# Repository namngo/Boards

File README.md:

# boards

## V1 

### Scope:

#### PCB

1. Use Esp32-s3 devboard.
1. Power directly from battery, not through battery pack (buck converter).
1. Front light: led driver.
1. Sensor: temperature.
1. LCD for information.
1. Box.
1. Button for light: off, auto, on.
1. Water proof.

Nice: Charge from bike charger.

Nice to have:

1. Backlight (red).
1. Button controller.

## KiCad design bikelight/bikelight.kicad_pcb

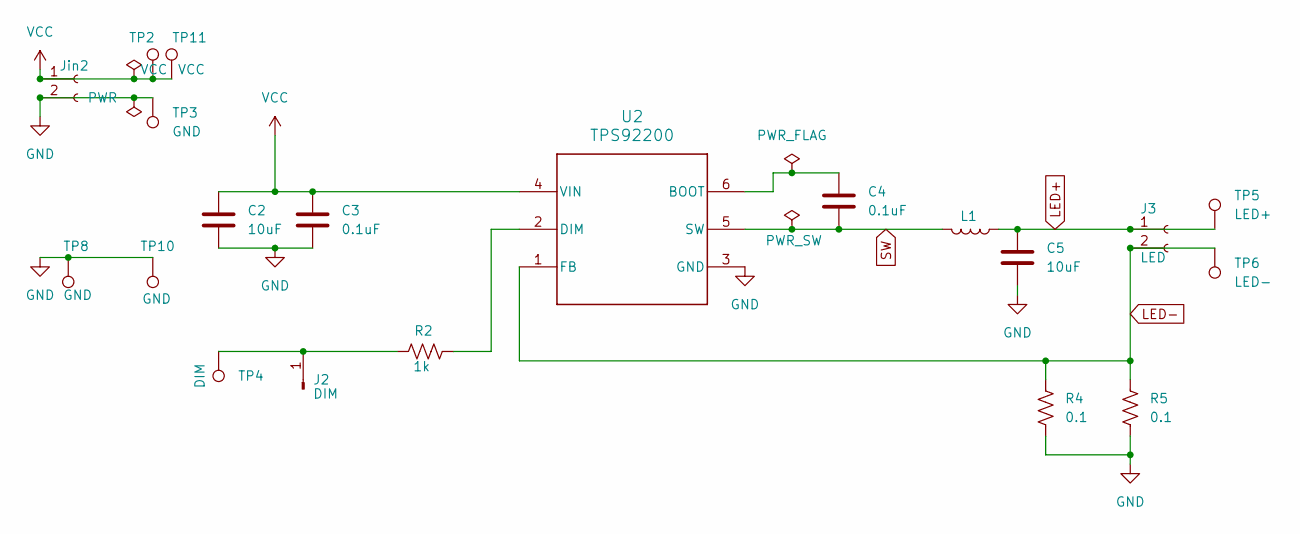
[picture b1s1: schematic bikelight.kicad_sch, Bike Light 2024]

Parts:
C2, C5: 10uF; C_1210_3225Metric
C3, C4: 0.1uF; C_0805_2012Metric
J2: DIM; PinHeader_1x01_P2.54mm_Vertical
J3: LED; PinHeader_1x02_P2.54mm_Vertical
Jin2: PWR; PinHeader_1x02_P2.54mm_Vertical
L1: L_Bourns_SRR1260
R2: 1k; R_0805_2012Metric
R4, R5: 0.1; R_1206_3216Metric
TP2, TP11: VCC; TestPoint_Pad_1.5x1.5mm
TP3, TP8, TP10: GND; TestPoint_Pad_1.5x1.5mm
TP4: DIM; TestPoint_Pad_1.5x1.5mm
TP5: LED+; TestPoint_Pad_1.5x1.5mm
TP6: LED-; TestPoint_Pad_1.5x1.5mm
U2: TPS92200; DDC0006A_N

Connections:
GND: C2.2, C3.2, C5.2, Jin2.2, R4.1, R5.1, TP3.1, TP8.1, TP10.1, U2.3 (GND)
LED+: C5.1, J3.1, L1.1, TP5.1
LED-: J3.2, R4.2, R5.2, TP6.1, U2.1 (FB)
unnamed: J2.1, R2.2, TP4.1
unnamed: C4.1, U2.6 (BOOT)
unnamed: R2.1, U2.2 (DIM)
SW: C4.2, L1.2, U2.5 (SW)
VCC: C2.1, C3.1, Jin2.1, TP2.1, TP11.1, U2.4 (VIN)

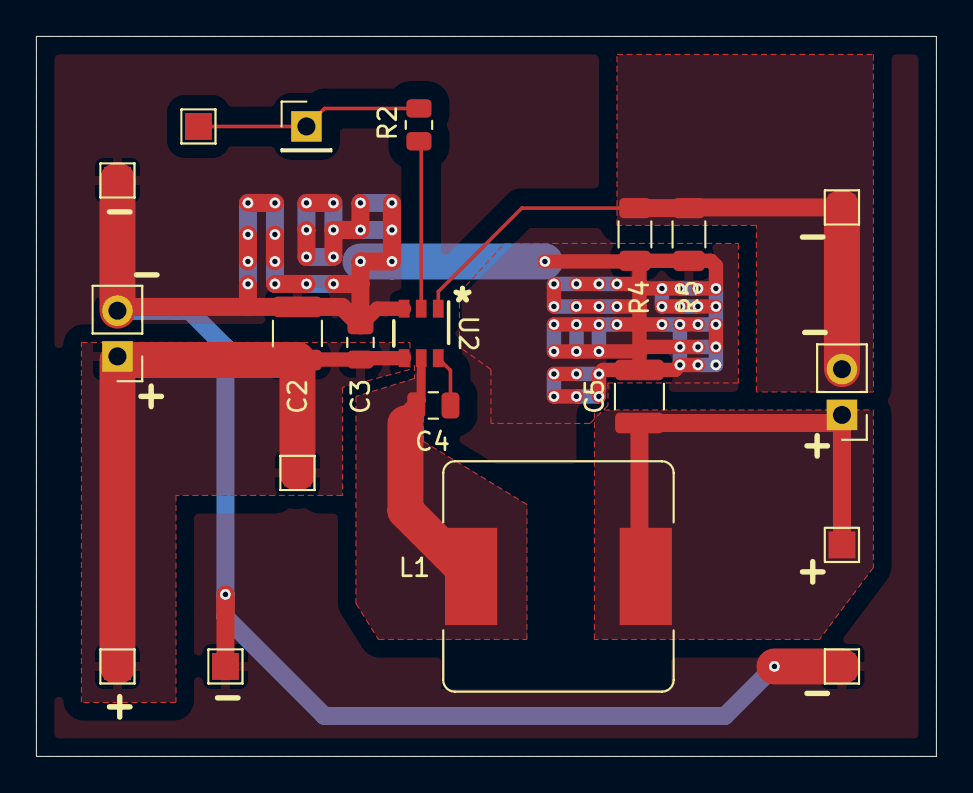
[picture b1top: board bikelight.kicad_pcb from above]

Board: 2 copper layers, 50.0 x 40.0 mm, 20 parts (0 on the bottom side), 8 nets.

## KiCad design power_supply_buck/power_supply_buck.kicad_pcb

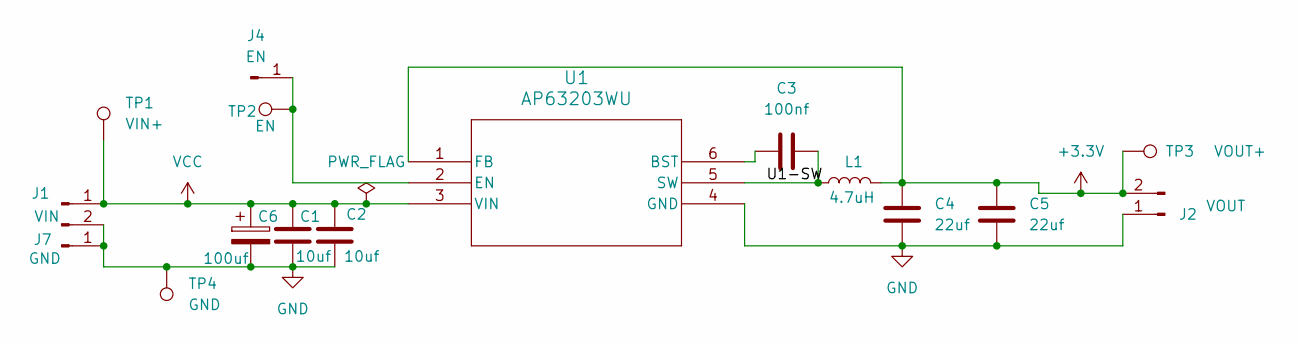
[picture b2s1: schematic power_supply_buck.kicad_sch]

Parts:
C1, C2: 10uf; C_1210_3225Metric_Pad1.33x2.70mm_HandSolder
C3: 100nf; C_0805_2012Metric_Pad1.18x1.45mm_HandSolder
C4, C5: 22uf; C_1210_3225Metric_Pad1.33x2.70mm_HandSolder
C6: 100uf; C_Elec_6.3x7.7
J1: VIN; PinHeader_1x02_P2.54mm_Vertical
J2: VOUT; PinHeader_1x02_P2.54mm_Vertical
J4: EN; PinHeader_1x01_P1.00mm_Vertical
J7: GND; PinHeader_1x01_P1.00mm_Vertical
L1: 4.7uH; L_Bourns_SRR1260
TP1: VIN+; TestPoint_Pad_1.0x1.0mm
TP2: EN; TestPoint_Pad_1.0x1.0mm
TP3: VOUT+; TestPoint_Pad_1.0x1.0mm
TP4: GND; TestPoint_Pad_1.0x1.0mm
U1: AP63203WU; AP63203WU-7_DIO

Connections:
+3.3V: C4.1, C5.1, J2.2, L1.2, TP3.1, U1.1 (FB)
/U1-SW: C3.2, L1.1, U1.5 (SW)
GND: C1.2, C2.2, C4.2, C5.2, C6.2, J1.2, J2.1, J7.1, TP4.1, U1.4 (GND)
unnamed: J4.1, TP2.1, U1.2 (EN)
unnamed: C3.1, U1.6 (BST)
VCC: C1.1, C2.1, C6.1, J1.1, TP1.1, U1.3 (VIN)

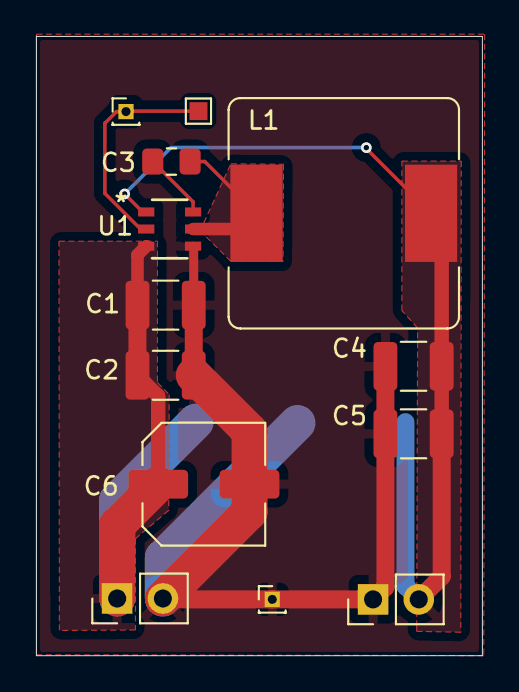
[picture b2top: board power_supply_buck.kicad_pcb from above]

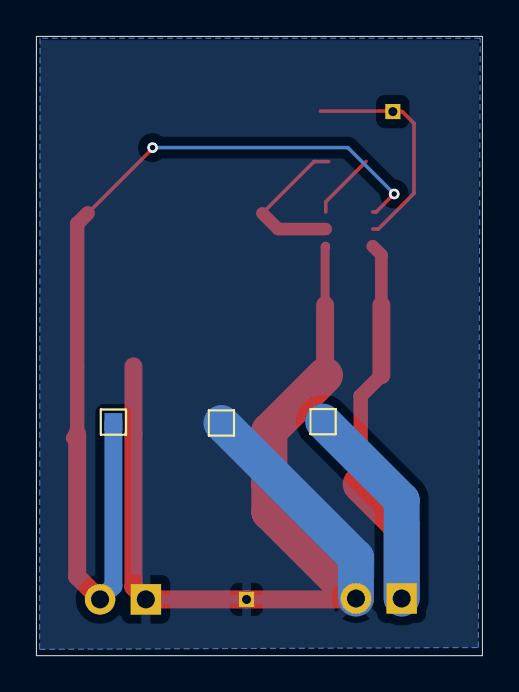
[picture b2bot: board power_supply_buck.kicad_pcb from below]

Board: 2 copper layers, 24.8 x 34.4 mm, 16 parts (3 on the bottom side), 6 nets.

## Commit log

2024-09-27 remove test file
2024-09-28 add some parts
2024-09-28 test points
2024-10-01 add new TPS92200D2DDCR parts
2024-10-03 update lights
2024-10-07 finish routing
2024-10-21 add a new power board
2024-10-22 footprint
2024-10-22 power supply
2024-11-01 done buck sch
2024-11-01 done sch
2024-11-01 done
2024-11-05 no footprint :(
2024-11-05 add u1 footprint
2024-11-05 routing
2025-12-24 finishing buck converter
2025-12-24 finish pour. Vias and labels
2025-12-30 add gerber
2026-03-05 esp32 big boards
